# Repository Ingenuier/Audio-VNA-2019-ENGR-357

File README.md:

# Audio-VNA-2019-ENGR-357
Audio Frequency VNA Project for Engineering Electronics II
Dominick Christensen

These are the setup instructions for the Reflection Bridge and Sound Card, these instructions were made with the Windows OS in mind.

These instructions and additional documentation can be found on the wiki : https://github.com/Ingenuier/Audio-VNA-2019-ENGR-357/wiki

Software Instructions:

    -git clone the repository ( https://github.com/Ingenuier/Audio-VNA-2019-ENGR-357.git )
    -Install Python 3.7.2 and your preferred tool for executing code 
        -In my tests Windows Powershell and JetBrain's PyCharm were used, in this instruction set we'll use PyCharm
    -In PyCharm, import:
        -NumPy
        -matplotlib
        -sounddevice
        -soundfile
    -Configure the VNAMain.py to execute through PyCharm

Hardware Instructions:

    -Plug in a 7.1 Ch Sound Card into your computer
    -Take two male to male 3.5 mm audio jacks and attach the soundcard output (headphones) into the input jack on the PCB
        -Do the same with the sound card input (microphone) and plug it into the output jack on the PCB
    -Use banana jack connectors to supply the PCB with +/- 15V and a connection to ground on a Power Supply
        -In my tests I used a HP Triple Output Power Supply
    -Use third male to male jack to connect the Device Under Test to the D.U.T Port on the PCB
    -Turn on the power and run the code on the PC

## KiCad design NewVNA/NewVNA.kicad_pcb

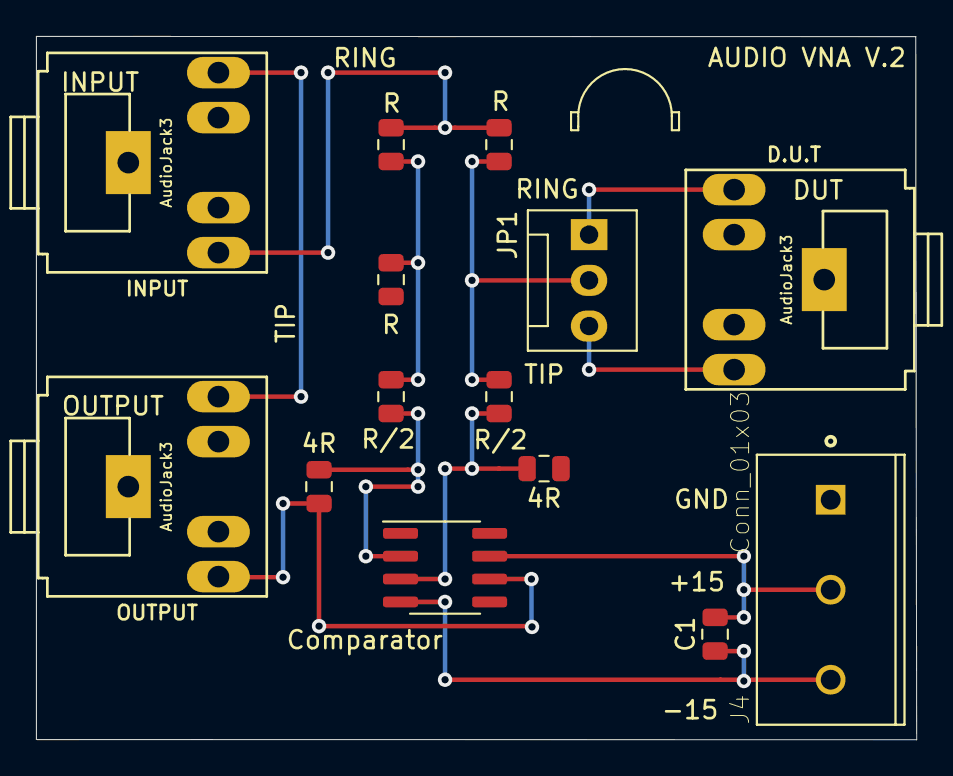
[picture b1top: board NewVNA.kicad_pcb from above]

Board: 2 copper layers, 48.9 x 39.1 mm, 14 parts (0 on the bottom side), 12 nets.

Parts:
4R, 4R#2: 4R; R_0805_2012Metric
C1: C; C_0805_2012Metric
Comparator: TL071; SOIC-8_3.9x4.9mm_P1.27mm
D.U.T: AudioJack3; Tayda_3.5mm_stereo_TRS_jack_A-853
INPUT: AudioJack3; Tayda_3.5mm_stereo_TRS_jack_A-853
J4: Conn_01x03; TE_282836-3
JP1: Jumper_3_Bridged12; FanPinHeader_1x03_P2.54mm_Vertical
OUTPUT: AudioJack3; Tayda_3.5mm_stereo_TRS_jack_A-853
R: R; R_0805_2012Metric
R#2, R#3: R; R_0805_2012Metric
R/2, R/2#2: R/2; R_0805_2012Metric

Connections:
+15V: C1.1, Comparator.7, J4.2
-15V: C1.2, Comparator.4, J4.3
GND: 4R.1, D.U.T.1, INPUT.1, J4.1, OUTPUT.1, R#2.2
unnamed: INPUT.2, OUTPUT.2
unnamed: 4R#2.2, Comparator.6, OUTPUT.3
unnamed: INPUT.3, R.1, R#3.1
unnamed: D.U.T.2, JP1.3
unnamed: D.U.T.3, JP1.1
unnamed: JP1.2, R.2, R/2.1
unnamed: 4R#2.1, Comparator.2, R/2#2.2
unnamed: R#2.1, R#3.2, R/2#2.1
unnamed: 4R.2, Comparator.3, R/2.2

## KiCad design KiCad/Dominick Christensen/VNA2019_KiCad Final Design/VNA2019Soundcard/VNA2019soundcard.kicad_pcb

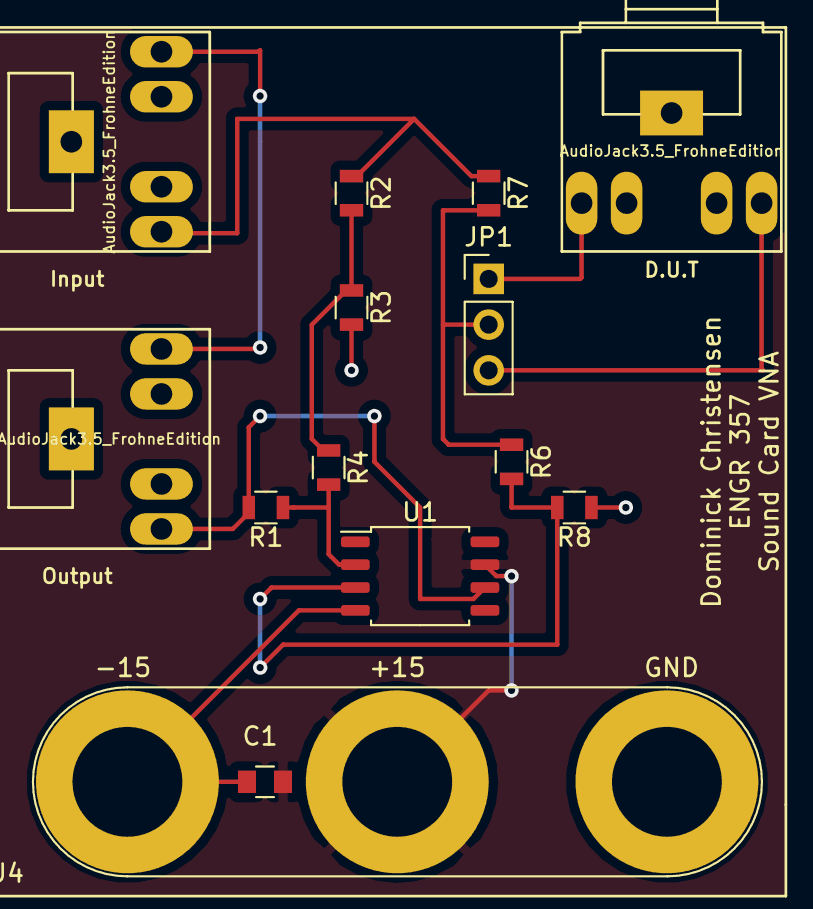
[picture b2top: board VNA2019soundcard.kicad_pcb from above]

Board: 2 copper layers, 14 parts (0 on the bottom side), 12 nets.

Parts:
C1: C; C_0805
D.U.T: AudioJack3.5_FrohneEdition; Tayda_3.5mm_stereo_TRS_jack_A-853
Input: AudioJack3.5_FrohneEdition; Tayda_3.5mm_stereo_TRS_jack_A-853
J4: Conn_01x03; Banana_Jack_3Pin
JP1: Jumper_3_Bridged12; PinHeader_1x03_P2.54mm_Vertical
Output: AudioJack3.5_FrohneEdition; Tayda_3.5mm_stereo_TRS_jack_A-853
R1, R2, R3, R4, R6, R7, R8: R; R_0805
U1: TL071; SOIC-8_5.23x5.23mm_P1.27mm

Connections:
+15V: C1.1, J4.2, U1.7
-15V: C1.2, J4.1, U1.4
GND: D.U.T.1, Input.1, J4.3, Output.1, R3.2, R8.1
unnamed: Input.2, Output.2
unnamed: Input.3, R2.1, R7.1
unnamed: Output.3, R1.2, U1.6
unnamed: D.U.T.2, JP1.3
unnamed: D.U.T.3, JP1.1
unnamed: JP1.2, R6.1, R7.2
unnamed: R1.1, R4.2, U1.2
unnamed: R2.2, R3.1, R4.1
unnamed: R6.2, R8.2, U1.3

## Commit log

2019-05-13 yeah
    python sound stuff
2019-05-13 Add files via upload
    Updated May 12, 2019 added ground and power to op amp. Successfully passed electrical rules test
2019-06-03 added my own version of the code
2019-06-03 added my kicad files -Dominick
2019-06-03 test please ignore
2019-06-03 recordAmplitude now replaced with leftAmplitude and rightAmplitude (unsure if right move)
2019-06-03 added plots
2019-06-04 commited some stuff
2019-06-04 Cleaned up the branch in preparation for the end
2019-06-04 created readme file for basic use instructions
    hopefully anybody who reads this 50 years from now won't have to hunt me down and demand answers from me on a long abandoned forum thread.
2019-06-04 added my name
    added my name to my version of the github readme file
2019-06-04 Latest Working Model, looks like the chop off alignment method may be the problem to never getting a negative gamma
2019-06-05 cleaned up CATVNAMAin, deleted unnecessary files
2019-06-05 Removing unnecessary files
2019-06-05 Cleaning up the repository
2019-06-06 Potential Fix to the code is to figure out how to remove imaginary parts from reflectmax and refmax without getting rid of the sign of the values
2019-06-07 Changes to VNAMain
2019-06-07 updated cart to pol functionality
2019-06-07 added photos folder for wiki writeup
2019-06-07 minor adjustments to kicad schem and also photos provided
2019-06-07 cleaning up the pcb schematic and some comments on the code
2019-06-07 Publishing VNAPCB for wiki
2019-06-10 Better Crop
2019-06-11 Tried adding smith charts, documentation on this subject foggier than expected.
